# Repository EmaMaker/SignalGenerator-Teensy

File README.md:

# Teensy 3.5 DDS Signal Generator
Using the integrated DAC of a Teensy 3.5 to generate arbitrary periodic waveforms<br>
This Signal Generator has been done as a project for my final High School Exam (Emanuele Coletta, ITIS Galileo Galilei Roma, a.s. 2020-2021) <br>

## How it works
The [Teensy 3.5](https://www.pjrc.com/store/teensy35.html) is a powerful Arduino-compatible microcontroller running an ARM Cortex-M4 at 120 MHz<br>
For the purpose of this project, it has been overclocked to 168MHz, running with the Fastest Pure Code+LTO optimizer<br>
It has two integrated DACs whose output can vary between 0v and 3.3V<br>
Using classical techniques from DDS (Direct Digital Synthesis) the Teensy can become a fully functional function generator<br>
In particular, the technique used here is the classic Phase Accumulator, together with a Lookup Table. This allows to precompute arbitrary periodic waveforms and then output them at the wanted frequency.<br>
Square waves of variable duty cycles can be generated by simply toggling a digital pin high and low and the correct time. Despite this, it's been chosen to use the DAC1 pin to generate square waves, which opens the possibility of using both DACs for arbitrary wave generation.
Despite both sine and square wave being output by the teensy are quite clean and seem to have low noise and spurs levels at naked eye, advanced filtering techniques, like Chebyshev, Butterworth or Bessel filters with multiple stages are required.
The desired waveform, frequency and duty cycle can be selected using the I2C LCD Display and an incremental encoder with pushbutton

## Why two different microcontrollers
Each and every clock cycle of the Teensy 3.5 is meticulously used to generate waveforms and have them to be precise in frequency over time. Therefore, no clock cycle can be wasted reading external input or driving the LCD Display. For this purpose, an AtMega32U4 handles the I2C LCD Display, the incremental encoder and the analog inputs from the output stage.

## Amplification and offset
Amplification is done using an OpAmp inverting configuration. The non-inverting pin is wired to a voltage divider made with a potentiometer which varies between -12V and +12V to offset the wave.
Using a peak detector the peak-to-peak voltage of the wave can be measured. An OpAmp in non-inverting summer configuration is used to sum the offset and the wave before the peak-detector: this allows to measure the peak no matter the offset condition. Furthermore, the use of opamps provides impeadence decoupling, isolating the measuring circuits from the output. The peak-to-peak and offset voltage of the wave are then remapped in the range 0-5V using an inverting OpAmp with a ratio of 1/5 whose non-inverting input is fixed at 2.5V. Those two signals are then fed back to an analogic input of the AtMega 32U4 to be shown on the LCD Display

## Filters
Filters have been generated using [The Filter Wizard by Analog Devices](https://tools.analog.com/en/filterwizard/). <br>
A 1st order RC passive low-pass filter has been choosen to smooth out the transitory of the square wave. Futhermore, this allows the use of DAC1 for arbitrary wave generation, even different from a square wave. <br>
A 6th order Butterworth low-pass filter has been choosen to smooth out the wave generated by the DAC. <br>

## Credits
A lot of choices come from following this Degree dissertation paper (Direct Digital Synthesizers: Theory, Design and Applications by Jouko Vankka, Helsinki University of Technology, November 2000): http://lib.tkk.fi/Diss/2000/isbn9512253186/isbn9512253186.pdf<br>
<br>Analog Devices offers a lot of cool guides and papers about DDS, this is one of them: https://www.analog.com/media/en/training-seminars/design-handbooks/Technical-Tutorial-DDS/Section8.pdf<br>
<br>The website [ZipCPU](zipcpu.com) offers a variety of articles about sine wave generation using FPGAs<br>
- https://zipcpu.com/dsp/2017/08/26/quarterwave.html<br>
- https://zipcpu.com/dsp/2017/07/11/simplest-sinewave-generator.html

<br>Stackoverflow and the rest of the internet of course<br>
- https://stackoverflow.com/questions/13466623/how-to-look-up-sine-of-different-frequencies-from-a-fixed-sized-lookup-table<br>
- https://stackoverflow.com/questions/16889426/fm-synthesis-using-phase-accumulator<br>
- https://electronics.stackexchange.com/questions/438935/how-to-calculate-sampling-rate-for-dac-from-its-data-sheet<br>
- https://www.daycounter.com/Calculators/Sine-Generator-Calculator.phtml<br>

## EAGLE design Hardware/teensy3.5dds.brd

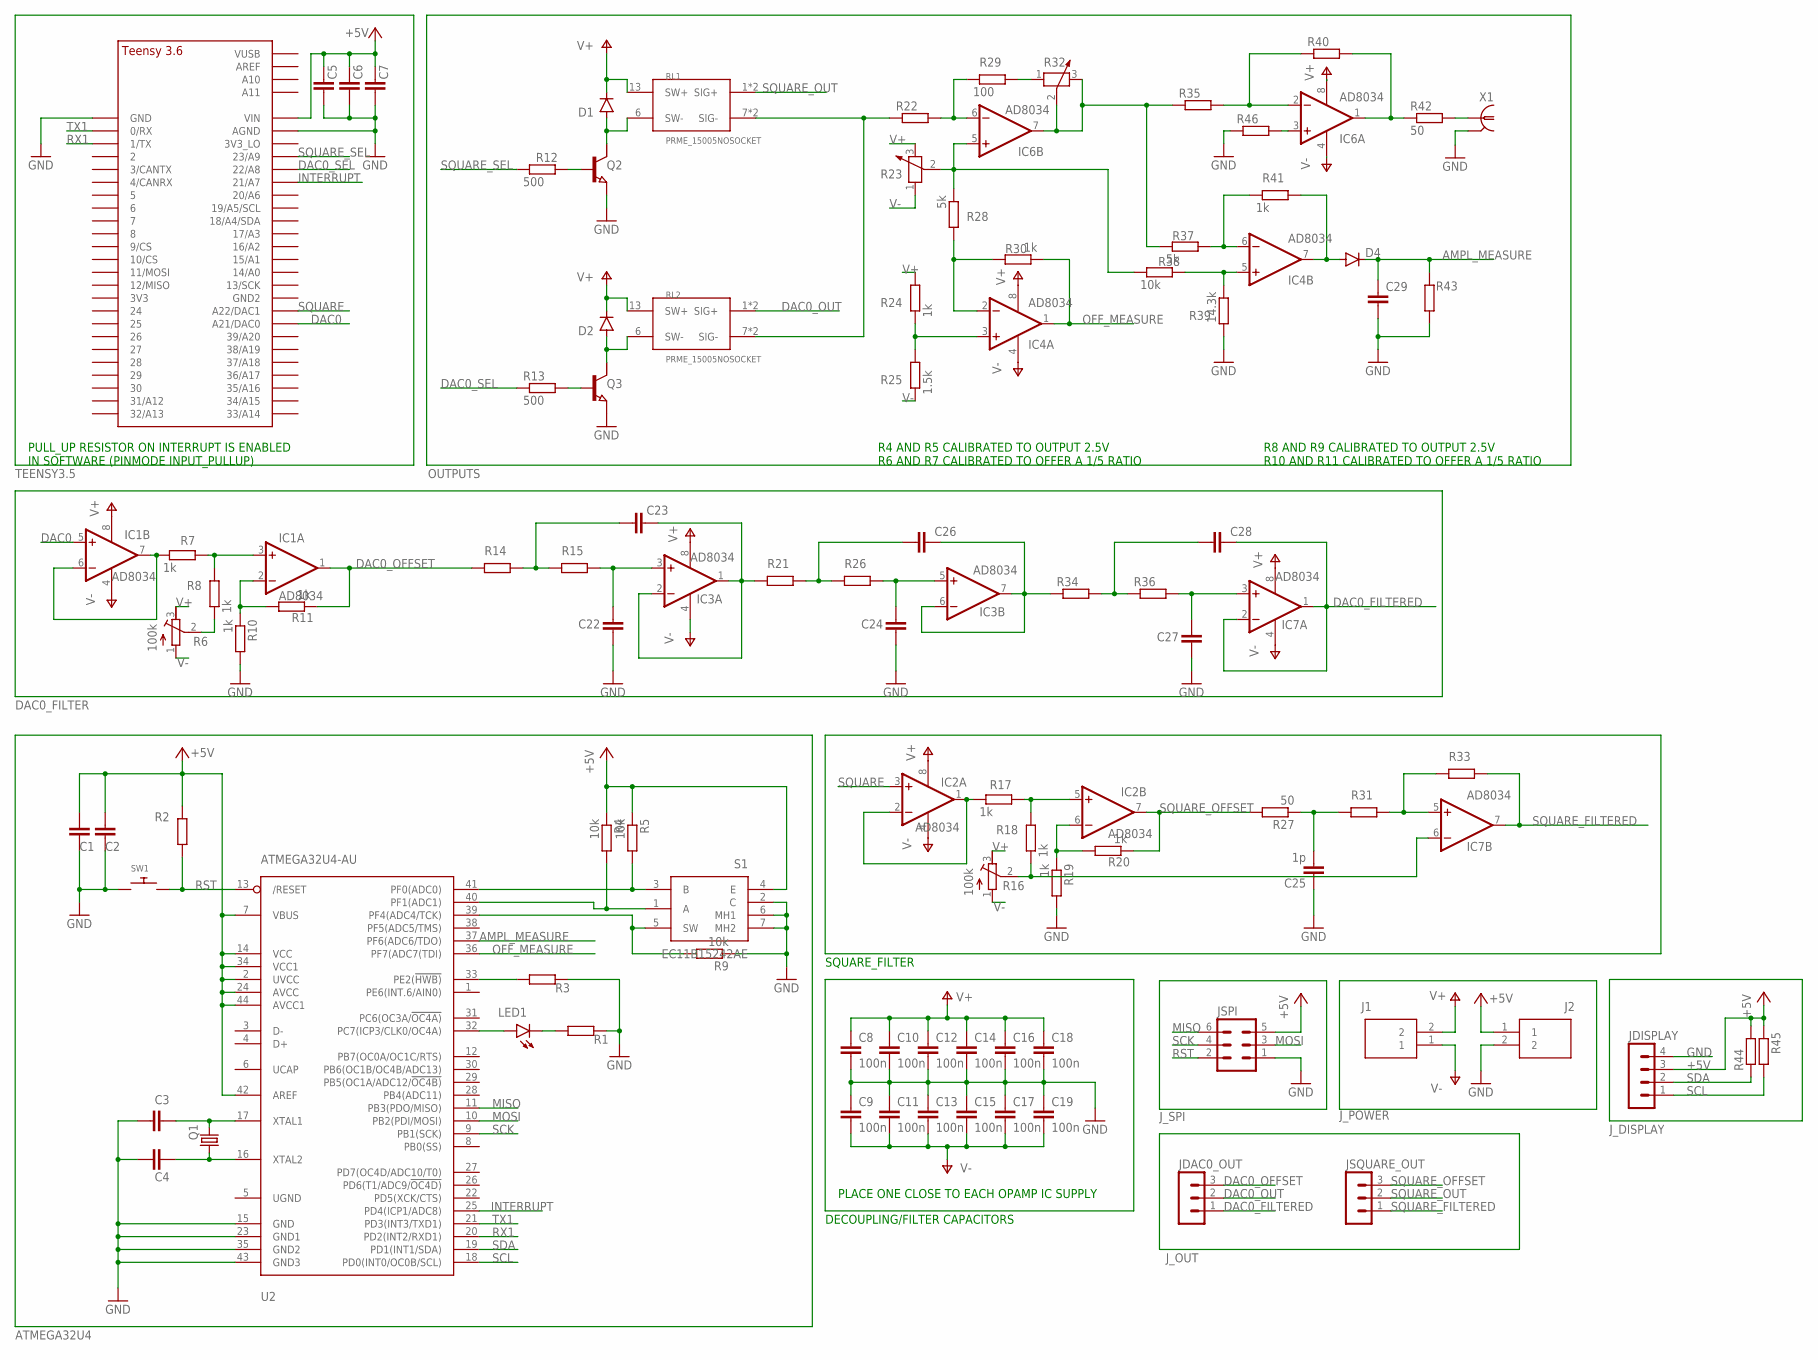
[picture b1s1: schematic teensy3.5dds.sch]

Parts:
C1, C5: 100u; C1206
C2, C6, C7, C8, C9, C10, C11, C12, C13, C14, C15, C16, C17, C18, C19: 100n; C0805
C3, C4: 22p; C0805
C22, C24, C27: 10p; C0805
C23: 150p; C0805
C25: 1p; C0805
C26, C28: 100p; C0805
C29: C-EUC0805; C0805
D1, D2: DIODE-SOD323-W; SOD323-W
D4: DIODE-SOD123; SOD123
IC1, IC2, IC3, IC4, IC6, IC7: AD8034; SO08
J1, J2: 1776275-2; 17762752
JDAC0_OUT: MA03-1
JDISPLAY: MA04-1
JSPI: MA03-2
JSQUARE_OUT: MA03-1
LED1: LEDCHIPLED_1206; CHIPLED_1206
Q1: 16MHz; CSM-7X-DU
Q2, Q3: NPN-TRANSISTIOR-2COLSOT89; SOT89
R1: 220; R0805
R2, R4, R5, R9, R33, R38: 10k; R0805
R3: 10k; M0805
R6, R16: 100k; RTRIM3296W
R7, R8, R10, R11, R17, R18, R19, R20, R22, R24, R30, R41: 1k; R0805
R12, R13: 500; R0805
R14, R15: 2.74k; R0805
R21: 787; R0805
R23, R32: 10k; MA03-1
R25: 1.5k; R0805
R26, R39: 14.3k; R0805
R27, R42: 50; R0805
R28, R37: 5k; R0805
R29: 100; R0805
R31: 2k; R0805
R34: 562; R0805
R35, R40, R43, R44, R45, R46: R-EU_R0805; R0805
R36: 20k; R0805
RL1, RL2: PRME_15005NOSOCKET; DIL14
S1: EC11B15242AE
SW1: SWITCH_PUSHBUTTONC&K_KSS; BTN_CK_KSS
U1: TEENSY_3.5/3.6_BASIC
U2: ATMEGA32U4-AU; TQFP44
X1: 1-227161-0; AMP_227161

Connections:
+5V: C1.1, C2.1, C5.1, C6.1, C7.1, J2.1, JDISPLAY.3, JSPI.5, R2.2, R4.1, R5.1, R44.2, R45.1, S1.4 (E), U1.VIN, U2.2 (UVCC), U2.7 (VBUS), U2.14 (VCC), U2.24 (AVCC), U2.34 (VCC1), U2.42 (AREF), U2.44 (AVCC1)
AMPL_MEASURE: C29.1, D4.C, R43.2, U2.37 (PF6(ADC6/TDO))
DAC0: IC1.5 (+IN), U1.21/DAC0 (A21/DAC0)
DAC0_FILTERED: C28.1, IC7.1 (OUT), IC7.2 (-IN), JDAC0_OUT.1
DAC0_OFFSET: IC1.1 (OUT), JDAC0_OUT.3, R11.1, R14.1
DAC0_OUT: JDAC0_OUT.2, RL2.1 (SIG+), RL2.14 (SIG+)
DAC0_SEL: R13.1, U1.22/A8
GND: C1.2, C2.2, C3.1, C4.1, C5.2, C6.2, C7.2, C8.2, C9.1, C10.2, C11.1, C12.2, C13.1, C14.2, C15.1, C16.2, C17.1, C18.2, C19.1, C22.1, C24.1, C25.1, C27.1, C29.2, J2.2, JDISPLAY.4, JSPI.1, Q2.3 (E), Q3.3 (E), R1.1, R3.2, R9.1, R10.2, R19.2, R39.2, R43.1, R46.1, S1.2 (C), S1.6 (MH1), S1.7 (MH2), SW1.P$1, U1.AGND, U1.GND, U2.15 (GND), U2.23 (GND1), U2.35 (GND2), U2.43 (GND3), X1.2
INTERRUPT: U1.21/A7, U2.25 (PD4(ICP1/ADC8))
MISO: JSPI.6, U2.11 (PB3(PDO/MISO))
MOSI: JSPI.3, U2.10 (PB2(PDI/MOSI))
unnamed: IC7.5 (+IN), R31.2, R33.1
unnamed: D1.A, Q2.2 (C), RL1.6 (SW-)
unnamed: IC6.5 (+IN), R23.2 (3), R28.1, R38.1
unnamed: C4.2, Q1.1, U2.16 (XTAL2)
unnamed: IC6.6 (-IN), R22.2, R29.1
unnamed: R42.2, X1.1
unnamed: R5.2, S1.3 (B), U2.41 (PF0(ADC0))
unnamed: IC6.7 (OUT), R32.2 (3), R32.3 (2), R35.1, R37.1
unnamed: R22.1, RL1.7 (SIG-), RL1.8 (SIG-), RL2.7 (SIG-), RL2.8 (SIG-)
unnamed: IC4.2 (-IN), R28.2, R30.2
unnamed: D2.A, Q3.2 (C), RL2.6 (SW-)
unnamed: IC4.3 (+IN), R24.1, R25.2
unnamed: IC4.5 (+IN), R38.2, R39.1
unnamed: R29.2, R32.1
unnamed: IC4.6 (-IN), R37.2, R41.1
unnamed: Q2.1 (B), R12.2
unnamed: Q3.1 (B), R13.2
unnamed: IC6.1 (OUT), R40.2, R42.1
unnamed: D4.A, IC4.7 (OUT), R41.2
unnamed: IC1.2 (-IN), R10.1, R11.2
unnamed: IC6.3 (+IN), R46.2
unnamed: IC1.6 (-IN), IC1.7 (OUT), R7.1
unnamed: IC2.6 (-IN), R19.1, R20.2
unnamed: R4.2, S1.1 (A), U2.40 (PF1(ADC1))
unnamed: IC1.3 (+IN), R7.2, R8.2
unnamed: IC2.1 (OUT), IC2.2 (-IN), R17.1
unnamed: IC2.5 (+IN), R17.2, R18.2
unnamed: R9.2, S1.5 (SW), U2.39 (PF4(ADC4/TCK))
unnamed: LED1.A, U2.32 (PC7(ICP3/CLK0/OC4A))
unnamed: C3.2, Q1.2, U2.17 (XTAL1)
unnamed: R3.1, U2.33 (PE2(!HWB))
unnamed: C25.2, R27.1, R31.1
unnamed: IC6.2 (-IN), R35.2, R40.1
unnamed: IC7.6 (-IN), R16.2 (S), R18.1
unnamed: LED1.C, R1.2
unnamed: C23.2, R14.2, R15.1
unnamed: C23.1, IC3.1 (OUT), IC3.2 (-IN), R21.1
unnamed: R6.2 (S), R8.1
unnamed: C22.2, IC3.3 (+IN), R15.2
unnamed: C26.1, R21.2, R26.1
unnamed: C26.2, IC3.6 (-IN), IC3.7 (OUT), R34.1
unnamed: C24.2, IC3.5 (+IN), R26.2
unnamed: C28.2, R34.2, R36.1
unnamed: C27.2, IC7.3 (+IN), R36.2
OFF_MEASURE: IC4.1 (OUT), R30.1, U2.36 (PF7(ADC7(TDI))
RST: JSPI.2, R2.1, SW1.P$2, U2.13 (/RESET)
RX1: U1.1/TX, U2.20 (PD2(INT2/RXD1))
SCK: JSPI.4, U2.9 (PB1(SCK))
SCL: JDISPLAY.1, R45.2, U2.18 (PD0(INT0/OC0B/SCL))
SDA: JDISPLAY.2, R44.1, U2.19 (PD1(INT1/SDA))
SQUARE: IC2.3 (+IN), U1.A22/DAC1
SQUARE_FILTERED: IC7.7 (OUT), JSQUARE_OUT.1, R33.2
SQUARE_OFFSET: IC2.7 (OUT), JSQUARE_OUT.3, R20.1, R27.2
SQUARE_OUT: JSQUARE_OUT.2, RL1.1 (SIG+), RL1.14 (SIG+)
SQUARE_SEL: R12.1, U1.23/A9
TX1: U1.0/RX, U2.21 (PD3(INT3/TXD1))
V+: C8.1, C10.1, C12.1, C14.1, C16.1, C18.1, D1.C, D2.C, IC1.8 (V+), IC2.8 (V+), IC3.8 (V+), IC4.8 (V+), IC6.8 (V+), IC7.8 (V+), J1.2, R6.3 (E), R16.3 (E), R23.3 (2), R24.2, RL1.13 (SW+), RL2.13 (SW+)
V-: C9.2, C11.2, C13.2, C15.2, C17.2, C19.2, IC1.4 (V-), IC2.4 (V-), IC3.4 (V-), IC4.4 (V-), IC6.4 (V-), IC7.4 (V-), J1.1, R6.1 (A), R16.1 (A), R23.1, R25.1

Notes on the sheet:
DECOUPLING/FILTER CAPACITORS
PLACE ONE CLOSE TO EACH OPAMP IC SUPPLY
R4 AND R5 CALIBRATED TO OUTPUT 2.5V R6 AND R7 CALIBRATED TO OFFER A 1/5 RATIO
R8 AND R9 CALIBRATED TO OUTPUT 2.5V R10 AND R11 CALIBRATED TO OFFER A 1/5 RATIO
PULL_UP RESISTOR ON INTERRUPT IS ENABLED IN SOFTWARE (PINMODE INPUT_PULLUP)
SQUARE_FILTER

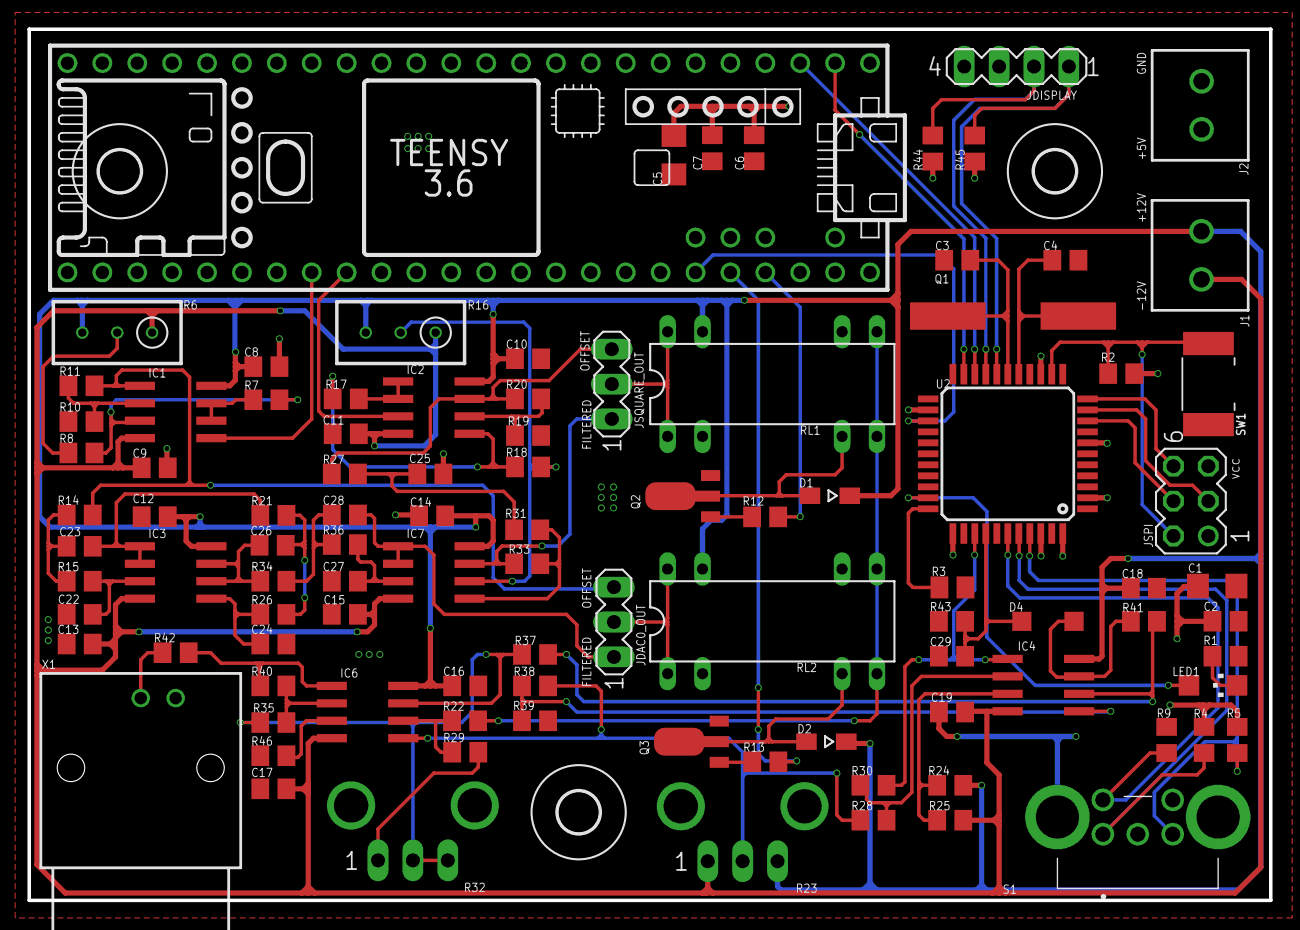
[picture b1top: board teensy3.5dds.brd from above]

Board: 2 copper layers, 90.4 x 63.4 mm, 102 parts (0 on the bottom side), 69 nets.

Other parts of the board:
U$1, U$3, U$4: 3,0

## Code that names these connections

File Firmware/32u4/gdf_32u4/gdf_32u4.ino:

#include <Encoder.h>
#include <Wire.h> 
#include <LiquidCrystal_I2C.h>
#include <Bounce2.h>

/*CONFIG*/
#define PUSHBUTTON A3
#define ENCODER_STEPS 5
#define TYPE_MIN 0
#define TYPE_MAX 1

#define OFF_MEASURE A0
#define AMPL_MEASURE A1

#define AMPL_MAX 5

#define DUTY_MIN 10
#define DUTY_MAX 90

#define MAX_ACHIEVABLE_FREQ 1000000
#define FREQ_ARRAY_LEN 7
#define INFO_UPDATE_TIME 2500

// Currently there's a pull up resistors, so it's inverted logic
#define PUSHBUTTON_HIGH LOW
#define PUSHBUTTON_LOW HIGH
/*----------------*/

/*INFO*/
unsigned long frequency = 1000, duty = 50, type = 0;
float Vpp = 6.4, Voff = 0.0;
/*-----------*/

int pushbutton, old_pushbutton;
boolean editingMode = false;

LiquidCrystal_I2C lcd(0x27,16,2);  // set the LCD address to 0x27 for a 16 chars and 2 line display
Encoder myEnc(A5, A4);
Bounce pushButton = Bounce();

void setup() {
  Serial1.begin(9600);

  pinMode(PUSHBUTTON, INPUT);
  pinMode(LED_BUILTIN, OUTPUT);
  pinMode(4, OUTPUT);
  
  lcd.init();
  lcd.backlight();

  lcd.setCursor(0,0);
  lcd.print("Teensy 3.5 DDS");
  lcd.setCursor(0,1);
  lcd.print("v1.0 by EmaMaker");

  delay(500);

  pushButton.attach(PUSHBUTTON);
  pushButton.interval(25);
  
  communicateChanges();
}

long enc_oldPosition  = -999, enc_newPosition;

void loop() {
  enc_newPosition = myEnc.read();
  pushButton.update();
  
  if(pushButton.fell() && !editingMode) editingMode = true;

  if(editingMode == true) editMode();
  else drawInfoOnScreen();
  
  if (enc_newPosition != enc_oldPosition) {
      enc_oldPosition = enc_newPosition;
  }
}


/*EDIT MODE*/
boolean cleared = false;

long current_digit = 0;
int editing_step = 0;
long* currently_editing;

boolean editing_digit = false;

String s;
long freq_digits[] = {1,0,0,0,0,0,0};

void editMode(){
  if(!cleared){
    lcd.clear();
    cleared = true;

    editing_step = 0;
    current_digit = 0;
    editing_digit = false;

    //Return now and start editing next cycle, otherwise the push button is read twice and type setting is skipped
    return;
  }

  if(editing_step == 0) {
    currently_editing = &type;
    
    lcd.setCursor(0,0);
    lcd.print("Type: ");
    switch(type){
      case 0:
        lcd.print("Sine      ");
        break;
      case 1:
        lcd.print("Square     ");
        break;
    }
  }else if(editing_step == 1) {
    if(type!=1) editing_step++;
    currently_editing = &duty;
    lcd.setCursor(0,0);
    lcd.print("Duty: ");
    lcd.print(duty);
    lcd.print("%     ");
  }else if(editing_step == 2) {
    lcd.setCursor(0,0);
    lcd.print("F: ");

    s = "";
    for(int i = 0; i < FREQ_ARRAY_LEN; i++){
      s += String(freq_digits[i]);
    }
    frequency = s.toInt();
    
    lcd.print(s + "Hz ");
    lcd.setCursor(13, 0);
    lcd.print("Ok?");

    lcd.setCursor(0,1);
    lcd.print("                 "); //clear line

    if(current_digit == FREQ_ARRAY_LEN) lcd.setCursor(15, 1);
    else lcd.setCursor(3+current_digit, 1);

    if(editing_digit) {
      currently_editing = &(freq_digits[current_digit]);
      freq_digits[current_digit] = constrain(freq_digits[current_digit], 0, 9);
      lcd.print("^");
    }else {
      lcd.print("_");
      currently_editing = &current_digit;
    }
    
  }else if(editing_step == 3){
    editingMode = false;
    cleared = false;

    delay(150);

    communicateChanges();
  }

  if (enc_newPosition < enc_oldPosition) (*currently_editing)--;
  else if (enc_newPosition > enc_oldPosition) (*currently_editing)++;

  type = constrain(type, TYPE_MIN, TYPE_MAX);
  duty = constrain(duty, DUTY_MIN, DUTY_MAX);
  current_digit = constrain(current_digit, 0, FREQ_ARRAY_LEN);

  if(pushButton.fell()) {
    if(editing_step != 2 || (editing_step == 2 && current_digit == FREQ_ARRAY_LEN)) editing_step++;
    else editing_digit = !editing_digit;
  }
}

void communicateChanges(){
  //First: toggle the interrupt pin until a positive response is received from teensy
  unsigned long t1 = millis();
  boolean b = false;

  Serial1.flush();
  digitalWrite(LED_BUILTIN, HIGH);
  while(Serial1.read() != 42){  //The answer to Life, Universe, And Everything Else
    if(millis() - t1 > 100){
      b = !b;
      t1 = millis();
      digitalWrite(4, b);
    }
  }
  digitalWrite(4, LOW );
  
  t1 = millis();
  /*How the communication protocol works:
  For simplicity, every information is send inside a string
  An information string starts with the character 'w' and ends 'W'
  Every information is added with a special character and terminator, the information is in between
  During construnction of the string, the construction functions are called and add the needed info*/
  
  String info = "w";

  info += "t" + String(type, DEC) + "T";
  info += "f" + String(frequency, DEC) + "F";
  info += "d" + String(duty, DEC) + "D";

  info += "W";
  
  lcd.clear();
  
  //Built the string with the info and set it to the teensy until a positive response is received
  Serial1.flush();
  
  while(Serial1.read() != 69){
    if(millis() - t1 > 250){
  
      lcd.setCursor(0,0);
      lcd.print(info);
      
      Serial1.print(info);
      t1 = millis();
    }
  }
  digitalWrite(LED_BUILTIN, LOW);
}


/*-------------*/

/*SHOW MODE*/
boolean b = true;
unsigned long t = 0;

void drawInfoOnScreen(){
  Voff = map_float(analogRead(OFF_MEASURE), 0, 1024, -12, 12);
  Vpp = 2*map_float(analogRead(AMPL_MEASURE), 0, 1024, 0, AMPL_MAX) + 0.3; //account for drop on shottky

  //Alternatevely, type and duty or frequency
  if(millis() - t > INFO_UPDATE_TIME) {
    b = !b;
    t = millis();
    lcd.clear();
  }
  
  //Amplitude, placeholder
  lcd.setCursor(0, 1);
  lcd.print("A:");
  lcd.print(String(Vpp, 1));
  lcd.print("V");

  //Offset
  lcd.setCursor(9, 1);
  lcd.print("O:");
  lcd.print(String(Voff, 1));
  lcd.print("V     ");
  
  if(b){
    lcd.setCursor(0,0);
    if(type == 0) lcd.print("Sine");
    else if(type == 1) lcd.print("Square");

    //16 - 8 chars for "Duty: __%" + 1 extra char if duty is 100
    lcd.setCursor(8-(duty==100), 0);
    lcd.print("Duty:");
    lcd.print(duty);
    lcd.print("%");
    
  }else{
    lcd.setCursor(0,0);
    lcd.print("Freq: ");
    lcd.print(frequency);
    lcd.print(" Hz");
  }
}

float map_float(float x, float in_min, float in_max, float out_min, float out_max) {
  return (x - in_min) * (out_max - out_min) / (in_max - in_min) + out_min;
}
/*-------------*/

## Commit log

2021-01-15 A bunch of tests with different approaches
2021-02-12 use microseconds for lower freq square waves
2021-02-12 handle lower frequency sine waves
2021-02-13 overclock and use fastest, pure code with lto
2021-02-13 optimize DAC using calling registers instead of analogWriteDAC0
    Take what's needed from framework's analogWriteDAC0
    A sine wave of 1MHz can now be generate without any problem
2021-02-13 Introduce README, move software into Firmware folder And create the still unused Hardware folder
2021-02-24 add support for dual channel sine waves
2021-03-07 hardware: Schematic v0.1 Still missing values for passive components Incomplete BoM Some trimmers need to be changed to vertically-positioned potentiometers
2021-03-07 hardware: better output select circuit And start arranging the components on the board
2021-03-09 hardware: switch to electronic opamp symbol * Add decoupling caps for each opamp IC * Change place to peak detector circuit, although the whole circuit needs to be changed
2021-03-09 hardware: add interrupt pin between 32u4 and teensy
2021-03-09 hardware: correct a few derps
2021-03-10 Revert "add support for dual channel sine waves"
    This reverts commit f3b1f87aa756bbdf2d2a4fc2abd1415255ae98b2.
2021-03-10 hardware: better relay switching circuit
2021-03-11 hardware: switch to AD737 instead of peak detector circuit Peak detector needed external impedance decoupling and would not have worked when the offset was different from 0 or when the amplification 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
2021-03-12 hardware: change some trimmers and potentiometers
2021-03-12 hardware: start arranging components on the board
2021-03-12 Schematic v0.2
2021-03-17 hardware: board v0.1
2021-03-18 hardware: board v0.2 shrink by 1cm on one side
2021-03-19 hardware: board v0.3 could it by shrinked a little bit on the shorter side?
2021-03-19 hardware: board v0.4 add M4 mounting holes
2021-03-19 hardware: add 50 Ohm resistor before BNC connector
2021-03-19 hardware: board v0.5 * shrink down to 11*8.5cm * Correct a few derps * Cumulative of caps changes on teensy and 32u4, add writes to output type choosing * Ignore overlap on transistors * Ignore AirWi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
2021-03-20 hardware: renumber parts * Label power connector on board
2021-03-28 little fixes
2021-03-28 an actually working filter for the square wave
2021-03-29 board redisegn
2021-04-02 fixes following the advice of people better than me at making PCBs
2021-04-12 board v1.0
2021-05-02 firmware: recalculate SAMPLE_FREQ for accurate frequency output
2021-05-16 initial docs
2021-05-16 hardware: board v2.0
    correct a few derps with missing resistors
    correct encoder pushbutton
    add i2c pullup resistors
    move some 32u4 pins to more accessible ones, supported by the arduino micro bootloader
    wire the 5v led to the builtin led on 32u4
    remove the ad737, move the a non-inverting summer circuit (wave+offset) with a peak finder to get the peak of the wave no matter the offset condition
2021-05-16 software: use DAC1 to generate square waves
2021-05-16 software: add 32u4 sketch
2021-05-16 firmware: add communication between 32u4 and teensy
2021-05-27 hardware: beautify schematic, add values
2021-05-27 Docs: progress
2021-05-27 hardware: beautify schematic and add values
2021-05-27 firmware: overclock teensy
2021-05-29 docs: add images
2021-05-29 firmware: always empty buffers when reading And recalculate SAMPLE_FREQ
2021-05-30 Update README.md
    Add images
2021-06-10 better square waves, still a bit unprecise in frequency
2021-06-11 simplify code
2021-06-14 firmware: clear buffers after end of communications
2021-06-14 firmware-32u4: add reading of offset and peak voltages
2021-06-14 firmware-teensy: default to none of the outputs selected
2021-06-17 firmware-32u4: just a couple more fixed before the exam
